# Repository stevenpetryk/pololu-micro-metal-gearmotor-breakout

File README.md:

# Pololu micro metal gearmotor connector breakout board

This is a breadboard-friendly breakout board specifically designed to work with the Pololu micro metal gearmotor encoders/connectors, specifically these two:

- [Magnetic Encoder Pair Kit with Side-Entry Connector for Micro Metal Gearmotors](https://www.pololu.com/product/4761)
- [Magnetic Encoder Pair Kit with Top-Entry Connector for Micro Metal Gearmotors](https://www.pololu.com/product/4760)

These two encoders are fitted with JST-SH connectors with a specific pinout. JST-SH connectors are a bit too small to solder 20 AWG wires too, so this breakout board makes them easier to work with.

The two headers are spaced by 0.3", so it takes up minimal space on a standard breadboard, and you can let the JST connectors "hang off" the end of the breadboard to save even more space.

## Pinout

- **VIN**: 2.7V to 18V DC. Both pins are connected, so you can wire up power to whichever side is more convenient.
- **GND**: Ground. Just like VIN, these two pins are connected, so you only need to ground one side.
- **ENC**: These are the "OUT A" and "OUT B" from the Pololu encoder datasheet, two for each side. These are the outputs of the quadrature encoders for each motor.
- **MOT**: These are "M1" and "M2" from the Pololu encoder datasheet, two for each side. Hook these up to the motor supply voltages. If you're using a microcontroller, I've found the DRV8833 dual motor driver works well with Pololu's micro metal gearmotors.

## Purchasing

You can [order this board on JLCPCB →][jlcpcb]

It's quite small, and only two layers, so it should only cost $2-$4 USD. I have some extras, so if you want, I'd happily mail one to you (unassembled), just [DM me on Twitter][twitter].

[jlcpcb]: https://cart.jlcpcb.com/quote?uploadNum=81e9938b29a3497882d0e2311ea6c4a7&businessType=example&fileName=gerber
[twitter]: https://twitter.com/stevenpetryk

## Bill of materials

It's surprisingly hard to find horizontal JST SMD connectors from anywhere but Sparkfun, so I tend to just order parts from there to save on shipping. They have bulk discounts, so if you're doing lots of work with micro metal gearmotors, just buy a bunch.

- [Sparkfun JST SH Horizontal 6-Pin Connector](https://www.sparkfun.com/products/10210)
- [Sparkfun break away headers](https://www.sparkfun.com/products/116)

## Dimensions

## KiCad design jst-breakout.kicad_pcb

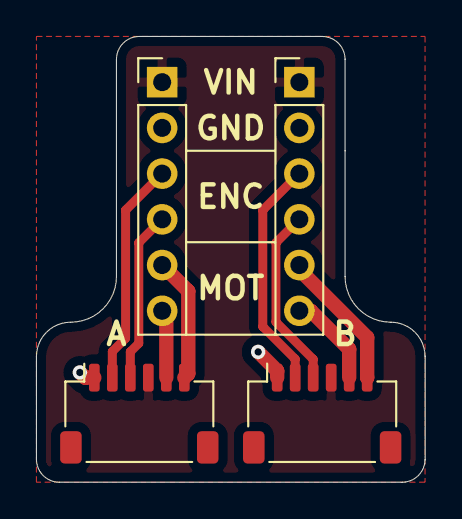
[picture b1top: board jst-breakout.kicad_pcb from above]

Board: 2 copper layers, 21.6 x 24.8 mm, 4 parts (0 on the bottom side), 10 nets.

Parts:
J1, J2: Conn_01x06; PinHeader_1x06_P2.54mm_Vertical
J3, J4: Conn_01x06; JST_SH_SM06B-SRSS-TB_1x06-1MP_P1.00mm_Horizontal

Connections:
/AENC1: J1.3, J3.2
/AENC2: J1.4, J3.3
/AIN1: J1.5, J3.6
/AIN2: J1.6, J3.5
/BENC1: J2.3, J4.2
/BENC2: J2.4, J4.3
/BIN1: J2.5, J4.6
/BIN2: J2.6, J4.5
GND: J1.2, J2.2, J3.1, J4.1
VCC: J1.1, J2.1, J3.4, J4.4

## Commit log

2020-07-11 Initial commit, v1
2020-07-11 Clarify product
2020-07-11 enhance
